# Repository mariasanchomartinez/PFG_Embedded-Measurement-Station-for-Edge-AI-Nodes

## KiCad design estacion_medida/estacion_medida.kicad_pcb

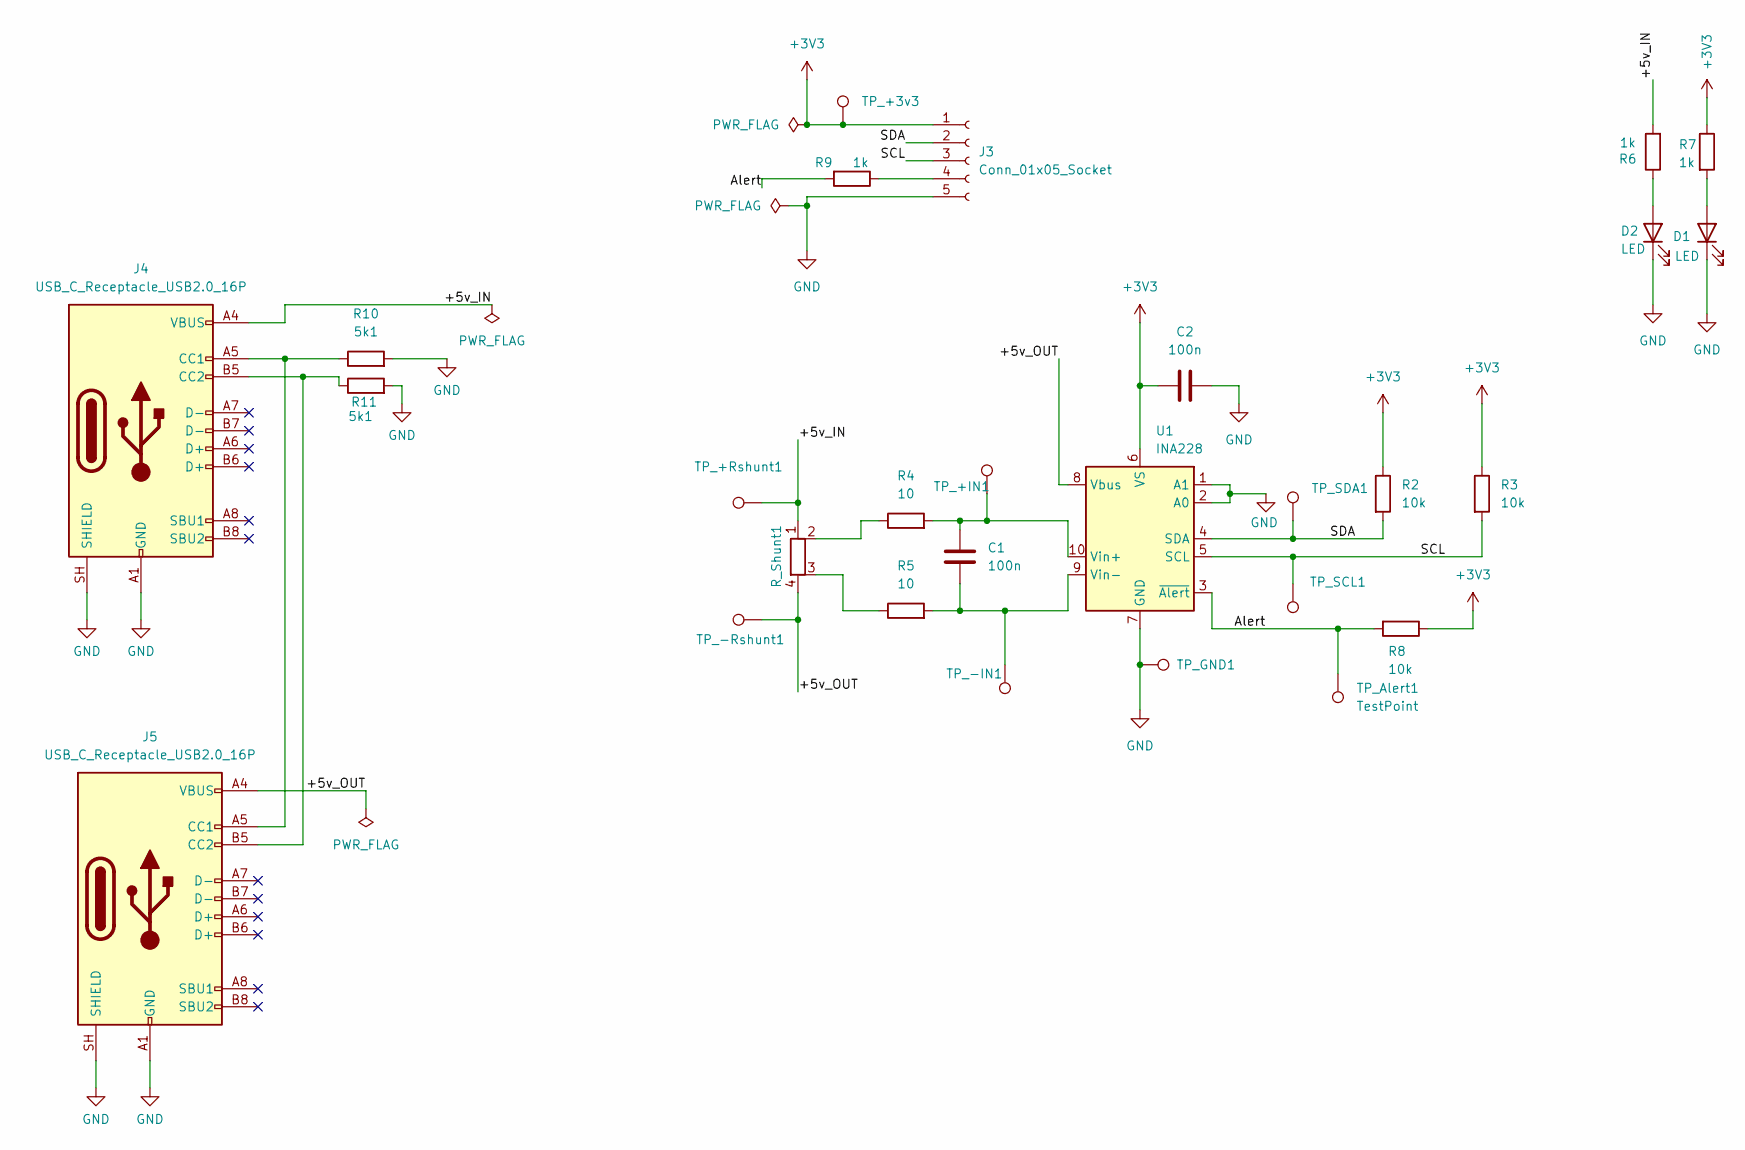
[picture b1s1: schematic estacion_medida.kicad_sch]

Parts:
C1, C2: 100n; C_1206_3216Metric
D1, D2: LED; LED_D3.0mm
J3: Conn_01x05_Socket; PinSocket_1x05_P2.54mm_Vertical
J4, J5: USB_C_Receptacle_USB2.0_16P; USB_C_Receptacle_HRO_TYPE-C-31-M-12
R2, R3, R8: 10k; R_1206_3216Metric
R4, R5: 10; R_0805_2012Metric
R6, R7: 1k; R_Axial_DIN0207_L6.3mm_D2.5mm_P10.16mm_Horizontal
R9: 1k; R_1206_3216Metric
R10, R11: 5k1; R_0603_1608Metric
R_Shunt1: 10mOhm; R_Shunt_Vishay_WSK2512_6332Metric_T2.21mm
TP_+3v3: TestPoint; Pin_D0.9mm_L10.0mm_W2.4mm_FlatFork
TP_+IN1: TestPoint; Pin_D0.9mm_L10.0mm_W2.4mm_FlatFork
TP_+Rshunt1: TestPoint; Pin_D0.9mm_L10.0mm_W2.4mm_FlatFork
TP_-IN1: TestPoint; Pin_D0.9mm_L10.0mm_W2.4mm_FlatFork
TP_-Rshunt1: TestPoint; Pin_D0.9mm_L10.0mm_W2.4mm_FlatFork
TP_Alert1: TestPoint; Pin_D0.9mm_L10.0mm_W2.4mm_FlatFork
TP_GND1: TestPoint; Pin_D0.9mm_L10.0mm_W2.4mm_FlatFork
TP_SCL1: TestPoint; Pin_D0.9mm_L10.0mm_W2.4mm_FlatFork
TP_SDA1: TestPoint; Pin_D0.9mm_L10.0mm_W2.4mm_FlatFork
U1: INA228; TSSOP-10_3x3mm_P0.5mm

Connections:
+3V3: C2.1, J3.1, R2.1, R3.1, R7.1, R8.1, TP_+3v3.1 (1_1), U1.6 (VS)
/+5v_IN: J4.A4 (VBUS), J4.A9 (VBUS), J4.B4 (VBUS), J4.B9 (VBUS), R6.2, R_Shunt1.1, TP_+Rshunt1.1 (1_1)
/+5v_OUT: J5.A4 (VBUS), J5.A9 (VBUS), J5.B4 (VBUS), J5.B9 (VBUS), R_Shunt1.4, TP_-Rshunt1.1 (1_1), U1.8 (Vbus)
/Alert: R8.2, R9.2, TP_Alert1.1 (1_1), U1.3 (~Alert)
/SCL: J3.3, R3.2, TP_SCL1.1 (1_1), U1.5 (SCL)
/SDA: J3.2, R2.2, TP_SDA1.1 (1_1), U1.4 (SDA)
GND: C2.2, D1.1 (K), D2.1 (K), J3.5, J4.A1 (GND), J4.A12 (GND), J4.B1 (GND), J4.B12 (GND), J4.SH (SHIELD), J5.A1 (GND), J5.A12 (GND), J5.B1 (GND), J5.B12 (GND), J5.SH (SHIELD), R10.2, R11.2, TP_GND1.1 (1_1), U1.1 (A1), U1.2 (A0), U1.7 (GND)
unnamed: D1.2 (A), R7.2
unnamed: D2.2 (A), R6.1
unnamed: J3.4, R9.1
unnamed: J4.A5 (CC1), J5.A5 (CC1), R10.1
unnamed: J4.B5 (CC2), J5.B5 (CC2), R11.1
unnamed: R4.1, R_Shunt1.2
unnamed: R5.1, R_Shunt1.3
unnamed: C1.1, R4.2, TP_+IN1.1 (1_1), U1.10 (Vin+)
unnamed: C1.2, R5.2, TP_-IN1.1 (1_1), U1.9 (Vin-)

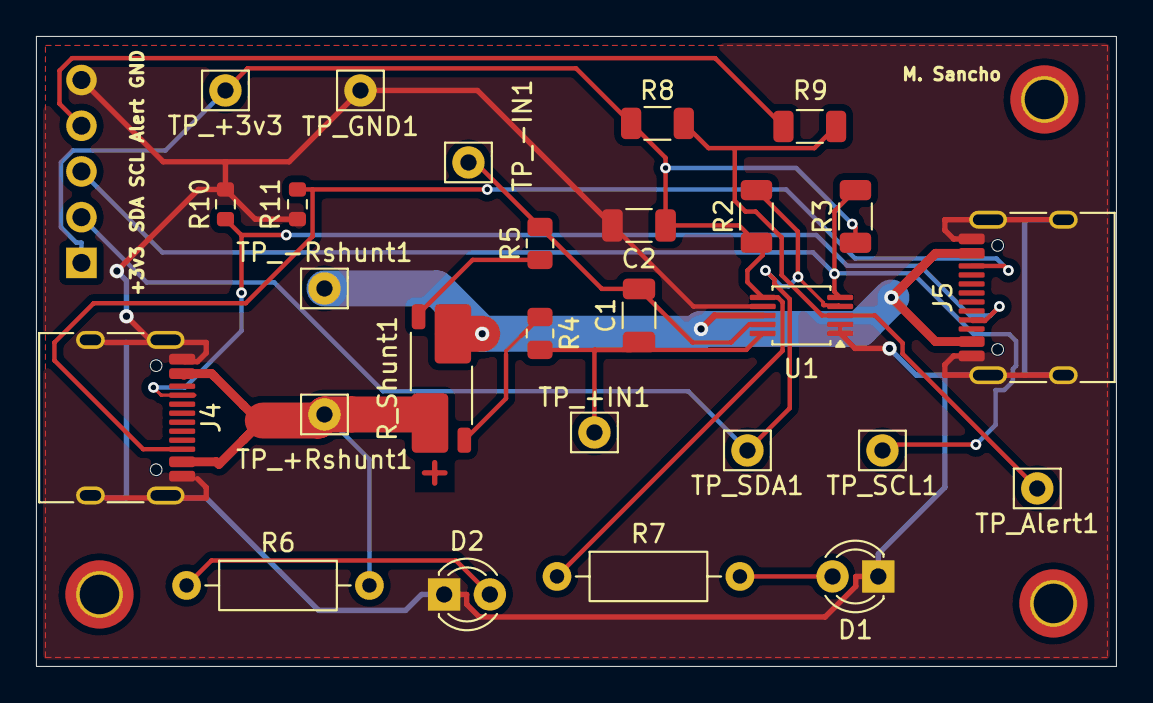
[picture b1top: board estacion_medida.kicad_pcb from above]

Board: 2 copper layers, 60.0 x 35.0 mm, 30 parts (1 on the bottom side), 16 nets.

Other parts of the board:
hole1, hole2: MountingHole_2.2mm_M2_DIN965_Pad_TopBottom

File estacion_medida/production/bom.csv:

Designator,Footprint,Quantity,Value,LCSC Part #
"C1, C2",1206,2,100n,
"D1, D2",LED_D3.0mm,2,LED,
J3,PinSocket_1x05_P2.54mm_Vertical,1,Conn_01x05_Socket,
"J4, J5",USB_C_Receptacle_HRO_TYPE-C-31-M-12,2,USB_C_Receptacle_USB2.0_16P,
"R10, R11",0603,2,5k1,
"R2, R3, R8",1206,3,10k,
"R4, R5",0805,2,10,
"R6, R7",R_Axial_DIN0207_L6.3mm_D2.5mm_P10.16mm_Horizontal,2,1k,
R9,1206,1,1k,
R_SHUNT1,R_Shunt_Vishay_WSK2512_6332Metric_T2.21mm,1,10mOhm,
"TP_+3V3, TP_+IN1, TP_+RSHUNT1, TP_-IN1, TP_-RSHUNT1, TP_ALERT1, TP_GND1, TP_SCL1, TP_SDA1",Pin_D0.9mm_L10.0mm_W2.4mm_FlatFork,9,TestPoint,
U1,TSSOP-10_3x3mm_P0.5mm,1,INA228,
